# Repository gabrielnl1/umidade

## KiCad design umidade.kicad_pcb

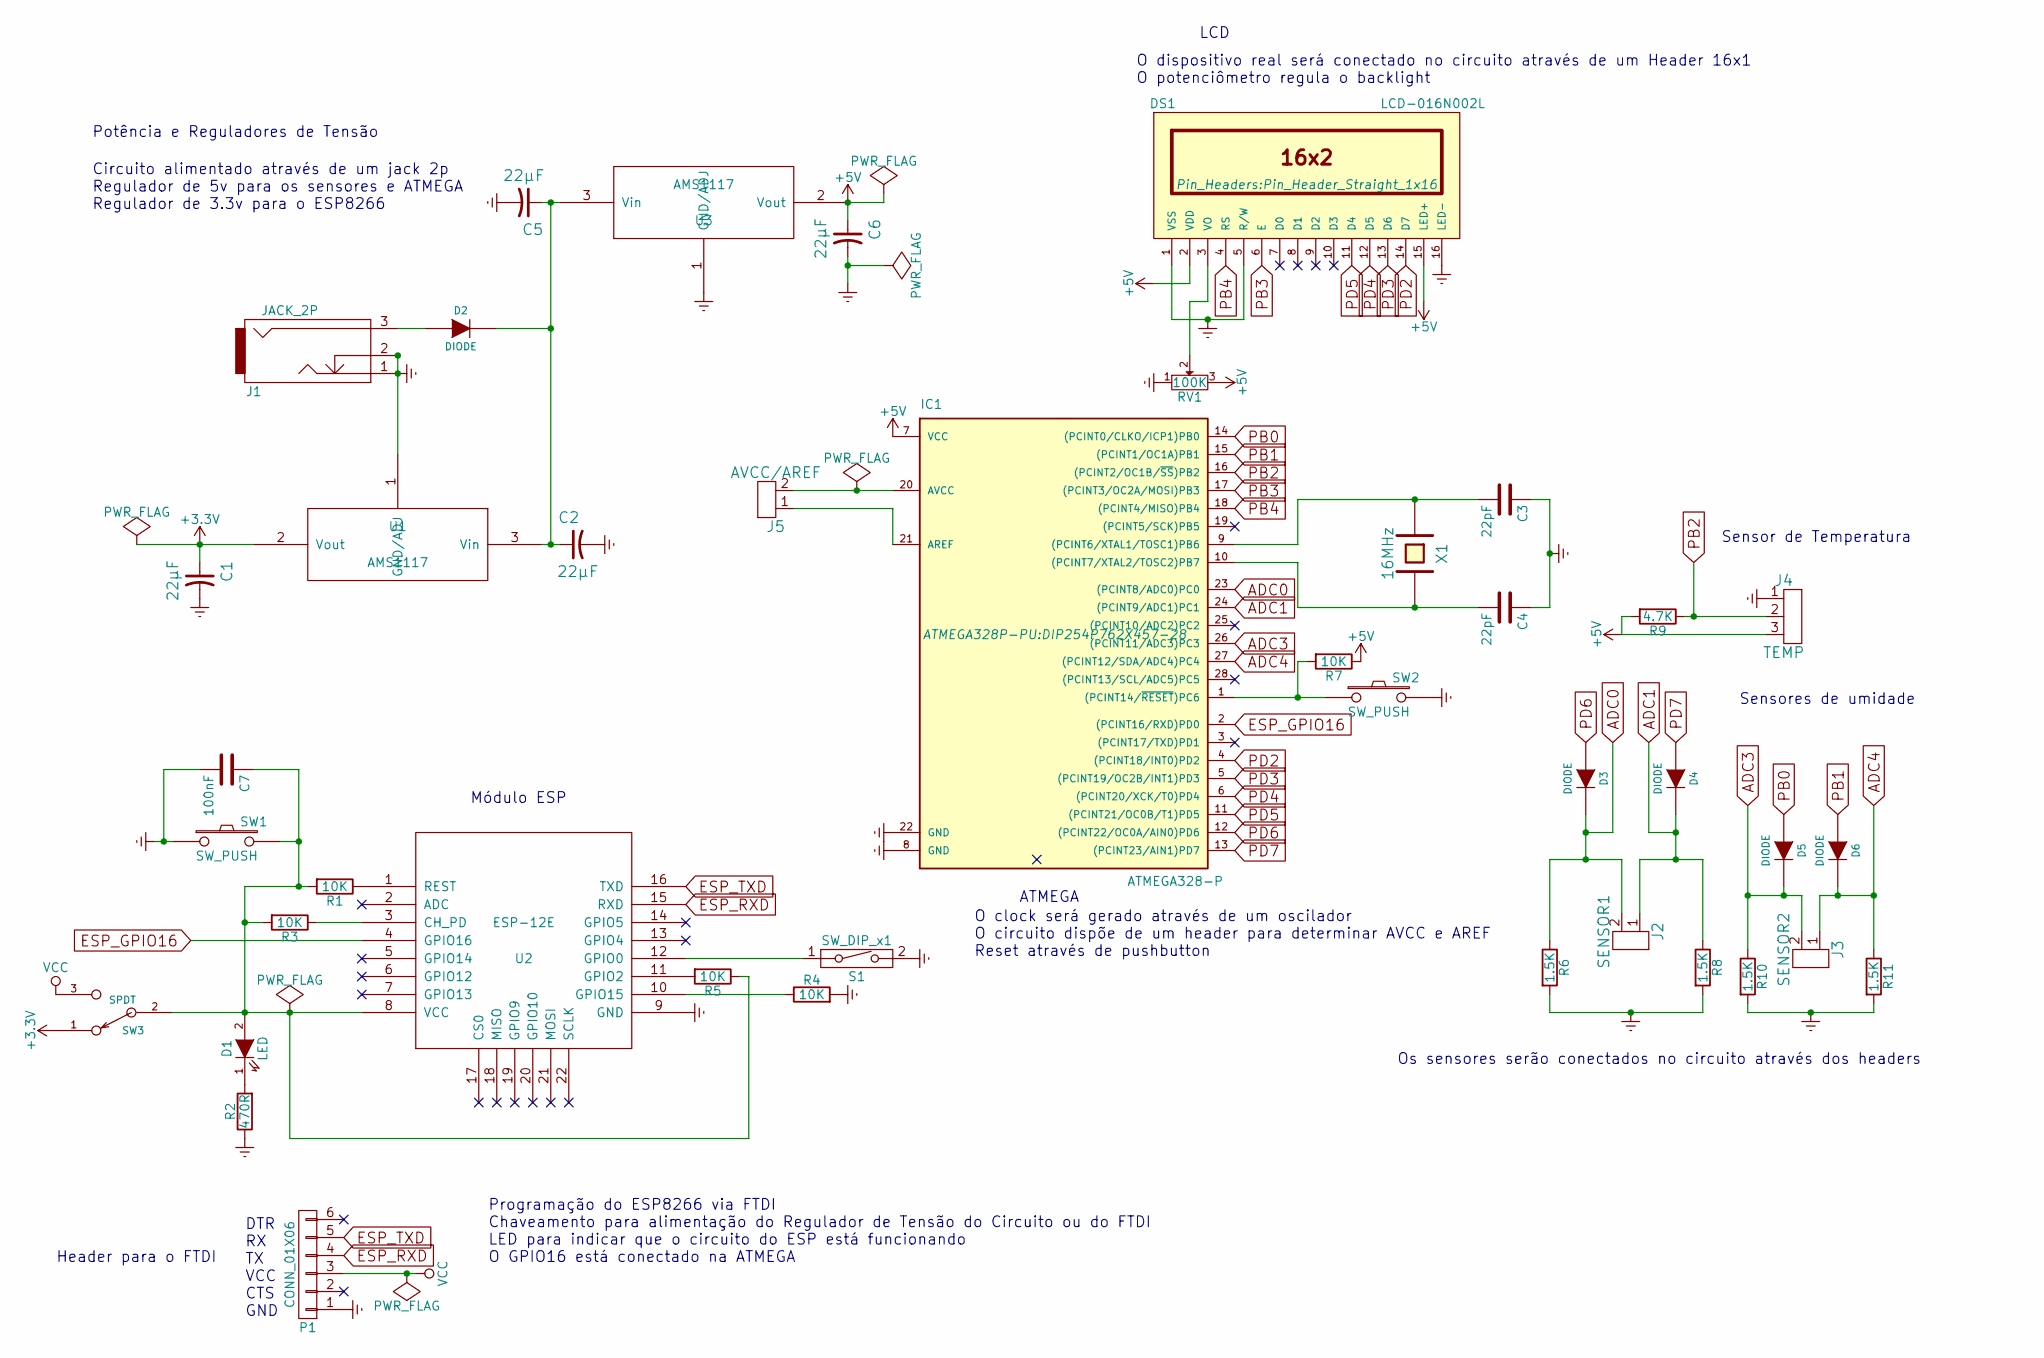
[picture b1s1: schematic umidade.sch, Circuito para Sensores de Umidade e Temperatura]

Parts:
C1, C2, C5, C6: 22μF; c_elec_5x5.3
C3, C4: 22pF; C_1206_HandSoldering
C7: 100nF; C_1206_HandSoldering
D1: LED; R_0805_HandSoldering
D2: DIODE; DO-214AC
D3, D4, D5, D6: DIODE; SOD-123
DS1: LCD-016N002L; Pin_Header_Straight_1x16
IC1: ATMEGA328-P; DIP254P762X457-28
J1: JACK_2P; BARREL_JACK_21x55
J2: SENSOR1; TerminalBlock_Pheonix_MPT-2.54mm_2pol
J3: SENSOR2; TerminalBlock_Pheonix_MPT-2.54mm_2pol
J4: TEMP; TerminalBlock_Pheonix_MPT-2.54mm_3pol
J5: AVCC/AREF; TerminalBlock_Pheonix_MPT-2.54mm_2pol
P1: CONN_01X06; Pin_Header_Straight_1x06
R1, R3, R4, R5, R7: 10K; R_0805_HandSoldering
R2: 470R; R_0805_HandSoldering
R6, R8, R10, R11: 1.5K; R_0805_HandSoldering
R9: 4.7K; R_0805_HandSoldering
RV1: 100K; Potentiometer_Trimmer_ACP_CA14v_Horizontal_Px15.0mm_Py10.0mm
S1: SW_DIP_x1; SW_Micro_SPST
SW1, SW2: SW_PUSH; SW_PUSH_6mm_h4.3mm
SW3: SPDT; SW_Micro_SPST
U1, U3: AMS1117; SOT-223
U2: ESP-12E
X1: 16MHz; Crystal_HC50-U_Vertical

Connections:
+3V3: C1.1, SW3.1, U1.2 (Vout)
+5V: C6.1, DS1.2 (VDD), DS1.15 (LED+), IC1.7 (VCC), J4.3, R7.1, R9.2, RV1.3, U3.2 (Vout)
ADC0: D3.2 (K), IC1.23 ((PCINT8/ADC0)PC0), J2.2, R6.1
ADC1: D4.2 (K), IC1.24 ((PCINT9/ADC1)PC1), J2.1, R8.1
ADC3: D5.2 (K), IC1.26 ((PCINT11/ADC3)PC3), J3.2, R10.1
ADC4: D6.2 (K), IC1.27 ((PCINT12/SDA/ADC4)PC4), J3.1, R11.1
ESP_GPIO16: IC1.2 ((PCINT16/RXD)PD0), U2.4 (GPIO16)
ESP_RXD: P1.4, U2.15 (RXD)
ESP_TXD: P1.5, U2.16 (TXD)
Earth: C1.2, C2.2, C3.1, C4.1, C5.2, C6.2, C7.2, DS1.1 (VSS), DS1.5 (R/W), DS1.16 (LED-), IC1.8 (GND), IC1.22 (GND), J1.1, J1.2, J4.1, P1.1, R2.1, R4.2, R6.2, R8.2, R10.2, R11.2, RV1.1, S1.2, SW1.1, SW2.2, U1.1 (GND/ADJ), U2.9 (GND), U3.1 (GND/ADJ)
unnamed: C2.1, C5.1, D2.2 (K), U1.3 (Vin), U3.3 (Vin)
unnamed: C3.2, IC1.9 ((PCINT6/XTAL1/TOSC1)PB6), X1.1
unnamed: C4.2, IC1.10 ((PCINT7/XTAL2/TOSC2)PB7), X1.2
unnamed: C7.1, D1.2 (A), R1.2, R3.2, R5.1, SW1.2, SW3.2, U2.8 (VCC)
unnamed: D1.1 (K), R2.2
unnamed: D2.1 (A), J1.3
unnamed: DS1.3 (VO), RV1.2
unnamed: IC1.1 ((PCINT14/~RESET~)PC6), R7.2, SW2.1
unnamed: IC1.20 (AVCC), J5.2
unnamed: IC1.21 (AREF), J5.1
unnamed: R1.1, U2.1 (REST)
unnamed: R3.1, U2.3 (CH_PD)
unnamed: R4.1, U2.10 (GPIO15)
unnamed: R5.2, U2.11 (GPIO2)
unnamed: S1.1, U2.12 (GPIO0)
PB0: D5.1 (A), IC1.14 ((PCINT0/CLKO/ICP1)PB0)
PB1: D6.1 (A), IC1.15 ((PCINT1/OC1A)PB1)
PB2: IC1.16 ((PCINT2/OC1B/~SS~)PB2), J4.2, R9.1
PB3: DS1.6 (E), IC1.17 ((PCINT3/OC2A/MOSI)PB3)
PB4: DS1.4 (RS), IC1.18 ((PCINT4/MISO)PB4)
PD2: DS1.14 (D7), IC1.4 ((PCINT18/INT0)PD2)
PD3: DS1.13 (D6), IC1.5 ((PCINT19/OC2B/INT1)PD3)
PD4: DS1.12 (D5), IC1.6 ((PCINT20/XCK/T0)PD4)
PD5: DS1.11 (D4), IC1.11 ((PCINT21/OC0B/T1)PD5)
PD6: D3.1 (A), IC1.12 ((PCINT22/OC0A/AIN0)PD6)
PD7: D4.1 (A), IC1.13 ((PCINT23/AIN1)PD7)
VCC: P1.3, SW3.3

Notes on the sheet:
DTR RX TX VCC CTS GND
Sensores de umidade
ATMEGA
LCD
Potência e Reguladores de Tensão
Header para o FTDI
Sensor de Temperatura
Módulo ESP
Circuito alimentado através de um jack 2p Regulador de 5v para os sensores e ATMEGA Regulador de 3.3v para o ESP8266
Programação do ESP8266 via FTDI Chaveamento para alimentação do Regulador de Tensão do Circuito ou do FTDI LED para indicar que o circuito do ESP está funcionando O GPIO16 está conectado na ATMEGA
O dispositivo real será conectado no circuito através de um Header 16x1 O potenciômetro regula o backlight
O clock será gerado através de um oscilador O circuito dispõe de um header para determinar AVCC e AREF Reset através de pushbutton
Os sensores serão conectados no circuito através dos headers

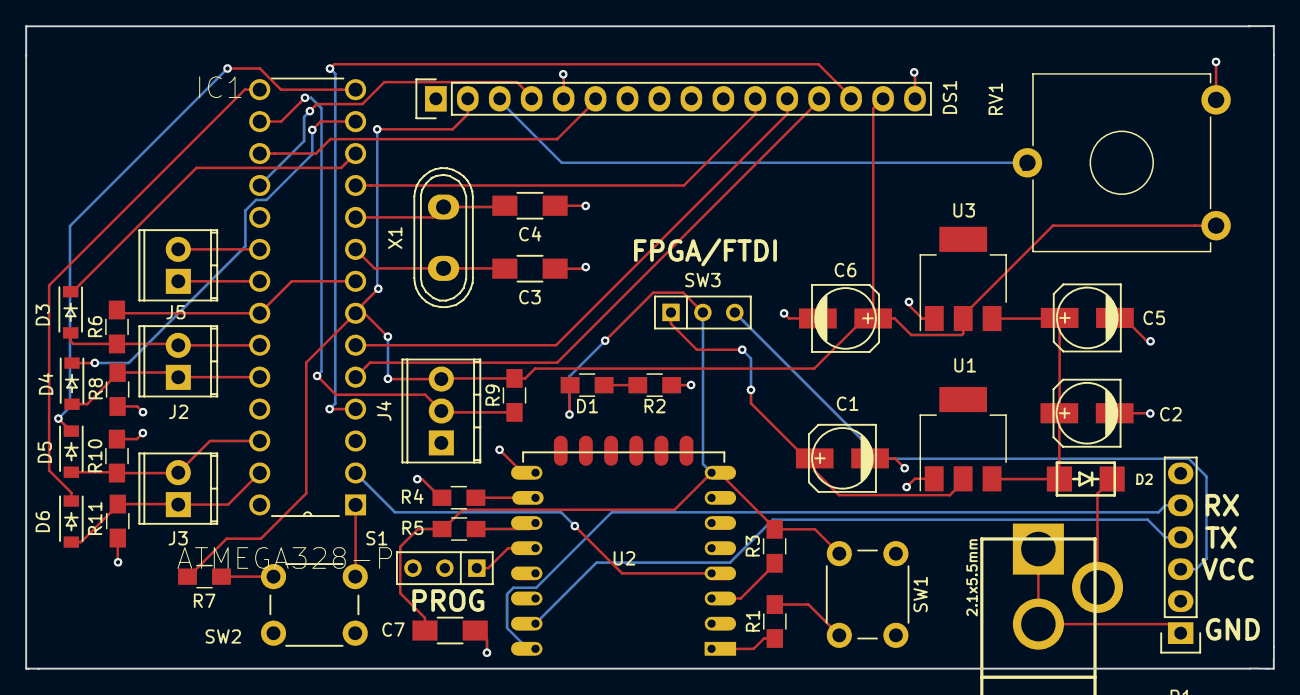
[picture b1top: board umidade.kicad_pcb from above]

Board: 2 copper layers, 99.2 x 51.1 mm, 41 parts (0 on the bottom side), 37 nets.

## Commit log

2017-11-06 1 commit
2017-11-06 2 commit
2017-11-16 2nd commit?
2017-11-27 revisao mais profissional
